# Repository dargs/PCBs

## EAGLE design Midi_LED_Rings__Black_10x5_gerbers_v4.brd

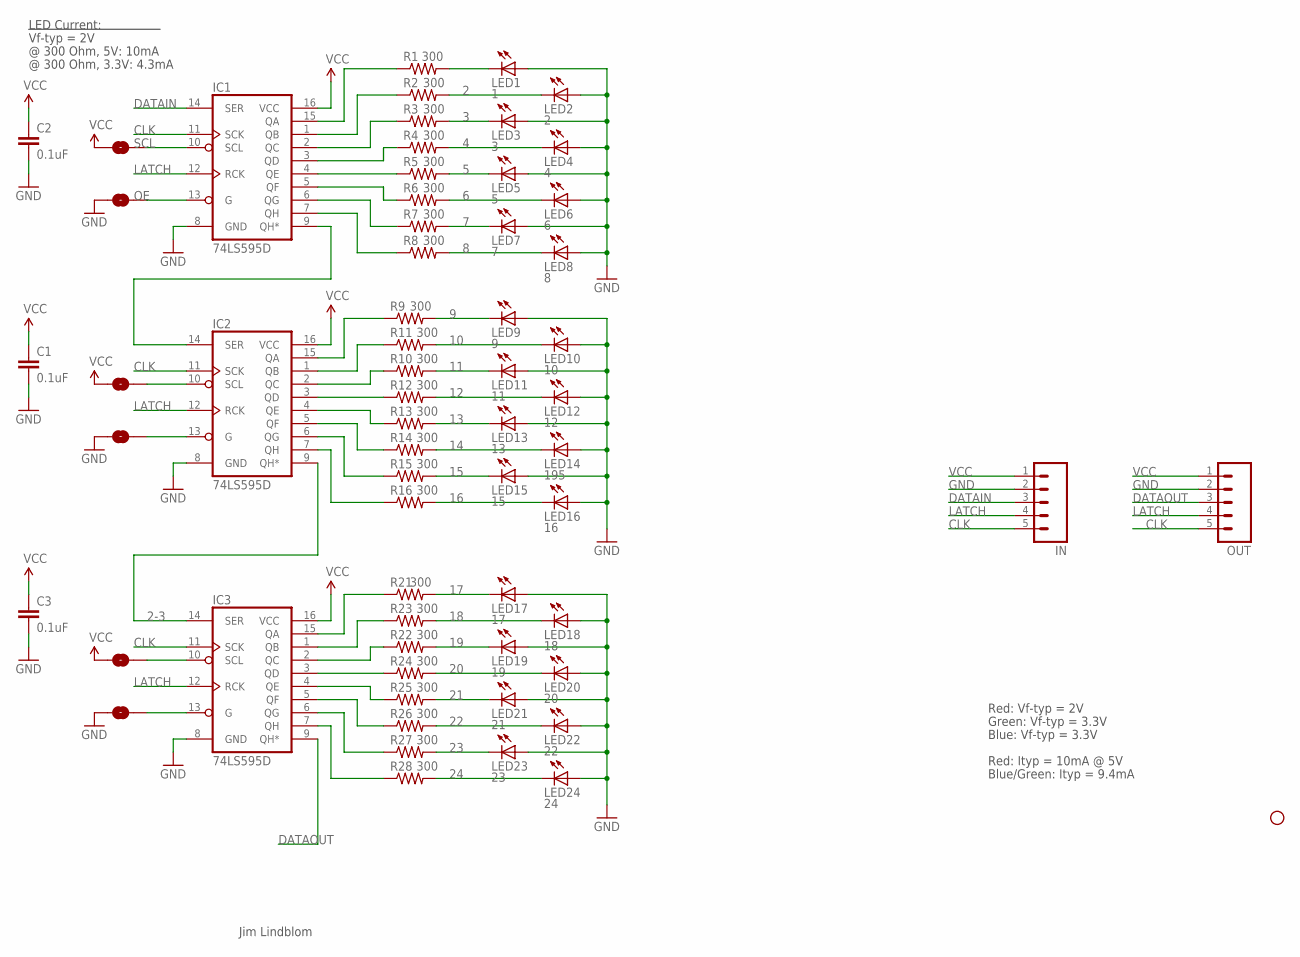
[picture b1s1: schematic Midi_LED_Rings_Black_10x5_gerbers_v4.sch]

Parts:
C1, C2, C3: 0.1uF; 0402-CAP
IC1, IC2, IC3: 74LS595D; SO16
IN: M05LOCK; 1X05_LOCK
JP12: STAND-OFF
LED1: 1; LED-1206
LED2: 2; LED-1206
LED3: 3; LED-1206
LED4: 4; LED-1206
LED5: 5; LED-1206
LED6: 6; LED-1206
LED7: 7; LED-1206
LED8: 8; LED-1206
LED9: 9; LED-1206
LED10: 10; LED-1206
LED11: 11; LED-1206
LED12: 12; LED-1206
LED13: 13; LED-1206
LED14: 195; LED-1206
LED15: 15; LED-1206
LED16: 16; LED-1206
LED17: 17; LED-1206
LED18: 18; LED-1206
LED19: 19; LED-1206
LED20: 20; LED-1206
LED21: 21; LED-1206
LED22: 22; LED-1206
LED23: 23; LED-1206
LED24: 24; LED-1206
OUT: M05LOCK; 1X05_LOCK
R1, R2, R3, R4, R5, R6, R7, R8, R9, R10, R11, R12, R13, R14, R15, R16, R21, R22, R23, R24, R25, R26, R27, R28: 300; 0805
SJ1, SJ2, SJ3, SJ4, SJ5, SJ6: SOLDERJUMPERTRACE; SJ_2S-TRACE

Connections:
1-2: IC1.9 (QH*), IC2.14 (SER)
2: LED2.C, R2.2
2-3: IC2.9 (QH*), IC3.14 (SER)
3: LED3.C, R3.2
4: LED4.C, R4.2
5: LED5.C, R5.2
6: LED6.C, R6.2
7: LED7.C, R7.2
8: LED8.C, R8.2
9: LED9.C, R9.2
10: LED10.C, R11.2
11: LED11.C, R10.2
12: LED12.C, R12.2
13: LED13.C, R13.2
14: LED14.C, R14.2
15: LED15.C, R15.2
16: LED16.C, R16.2
17: LED17.C, R21.2
18: LED18.C, R23.2
19: LED19.C, R22.2
20: LED20.C, R24.2
21: LED21.C, R25.2
22: LED22.C, R26.2
23: LED23.C, R27.2
24: LED24.C, R28.2
CLK: IC1.11 (SCK), IC2.11 (SCK), IC3.11 (SCK), IN.5, OUT.5
DATAIN: IC1.14 (SER), IN.3
DATAOUT: IC3.9 (QH*), OUT.3
GND: C1.2, C2.2, C3.2, IC1.8 (GND), IC2.8 (GND), IC3.8 (GND), IN.2, LED1.A, LED2.A, LED3.A, LED4.A, LED5.A, LED6.A, LED7.A, LED8.A, LED9.A, LED10.A, LED11.A, LED12.A, LED13.A, LED14.A, LED15.A, LED16.A, LED17.A, LED18.A, LED19.A, LED20.A, LED21.A, LED22.A, LED23.A, LED24.A, OUT.2, SJ2.1, SJ4.1, SJ6.1
LATCH: IC1.12 (RCK), IC2.12 (RCK), IC3.12 (RCK), IN.4, OUT.4
unnamed: IC1.15 (QA), R1.1
unnamed: IC1.1 (QB), R2.1
unnamed: IC1.2 (QC), R3.1
unnamed: IC1.3 (QD), R4.1
unnamed: IC1.4 (QE), R5.1
unnamed: IC1.5 (QF), R6.1
unnamed: IC1.6 (QG), R7.1
unnamed: IC1.7 (QH), R8.1
unnamed: IC2.15 (QA), R9.1
unnamed: IC2.1 (QB), R11.1
unnamed: IC2.2 (QC), R10.1
unnamed: IC2.3 (QD), R12.1
unnamed: IC2.4 (QE), R13.1
unnamed: IC2.5 (QF), R14.1
unnamed: IC2.6 (QG), R15.1
unnamed: IC2.7 (QH), R16.1
unnamed: IC3.15 (QA), R21.1
unnamed: IC3.1 (QB), R23.1
unnamed: IC3.2 (QC), R22.1
unnamed: IC3.3 (QD), R24.1
unnamed: IC3.4 (QE), R25.1
unnamed: IC3.5 (QF), R26.1
unnamed: IC3.6 (QG), R27.1
unnamed: IC3.7 (QH), R28.1
unnamed: IC2.13 (G), SJ4.2
unnamed: IC2.10 (SCL), SJ3.2
unnamed: IC3.10 (SCL), SJ5.2
unnamed: IC3.13 (G), SJ6.2
unnamed: LED1.C, R1.2
OE: IC1.13 (G), SJ2.2
SCL: IC1.10 (SCL), SJ1.2
VCC: C1.1, C2.1, C3.1, IC1.16 (VCC), IC2.16 (VCC), IC3.16 (VCC), IN.1, OUT.1, SJ1.1, SJ3.1, SJ5.1

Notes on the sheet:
Jim Lindblom
Vf-typ = 2V
@ 300 Ohm, 5V: 10mA
LED Current:
Red: Vf-typ = 2V
Green: Vf-typ = 3.3V
Blue: Vf-typ = 3.3V
@ 300 Ohm, 3.3V: 4.3mA
Red: Ityp = 10mA @ 5V
Blue/Green: Ityp = 9.4mA

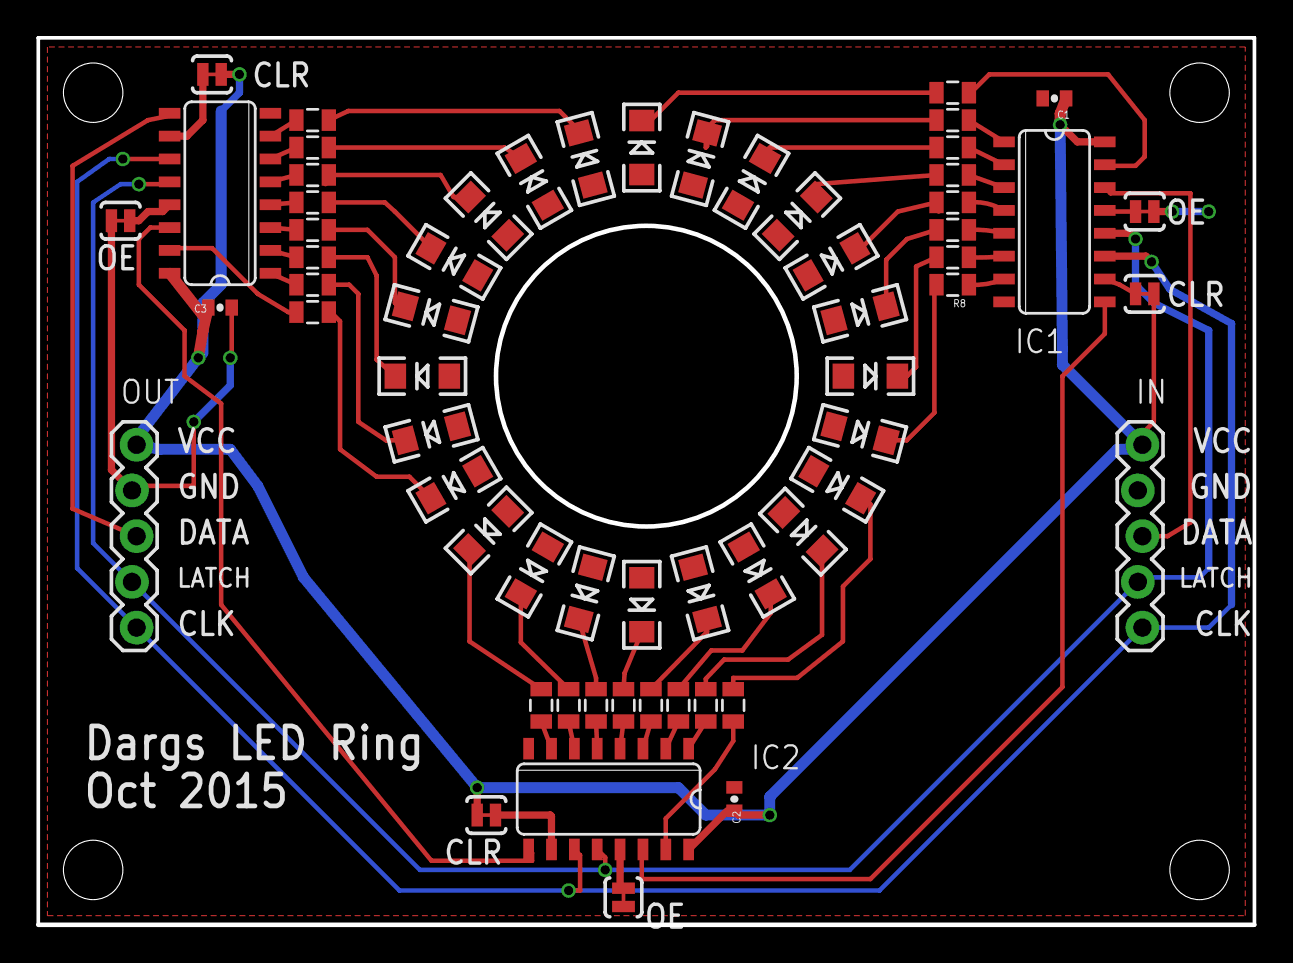
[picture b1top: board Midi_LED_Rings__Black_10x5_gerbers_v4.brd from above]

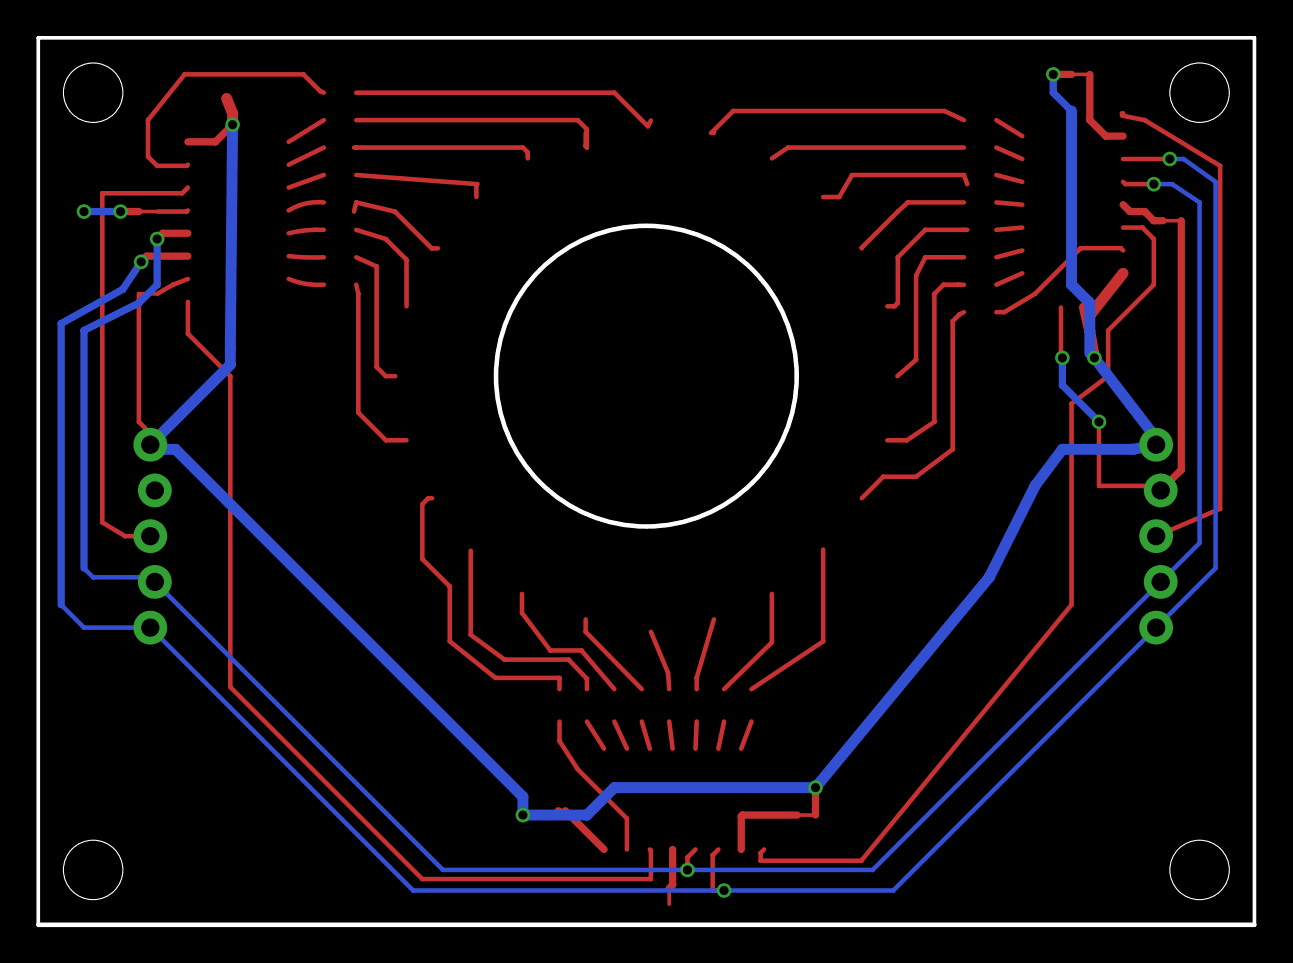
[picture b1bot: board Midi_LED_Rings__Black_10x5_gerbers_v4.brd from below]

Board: 2 copper layers, 67.6 x 49.3 mm, 66 parts (4 on the bottom side), 62 nets.

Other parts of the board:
JP1, JP10, JP11: STAND-OFF

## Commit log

2015-11-15 Master
    master

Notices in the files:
parts and their libraries:
SparkFun-LED: Licensing: Creative Commons ShareAlike 4.0 International - https://creativecommons.org/licenses/by-sa/4.0
